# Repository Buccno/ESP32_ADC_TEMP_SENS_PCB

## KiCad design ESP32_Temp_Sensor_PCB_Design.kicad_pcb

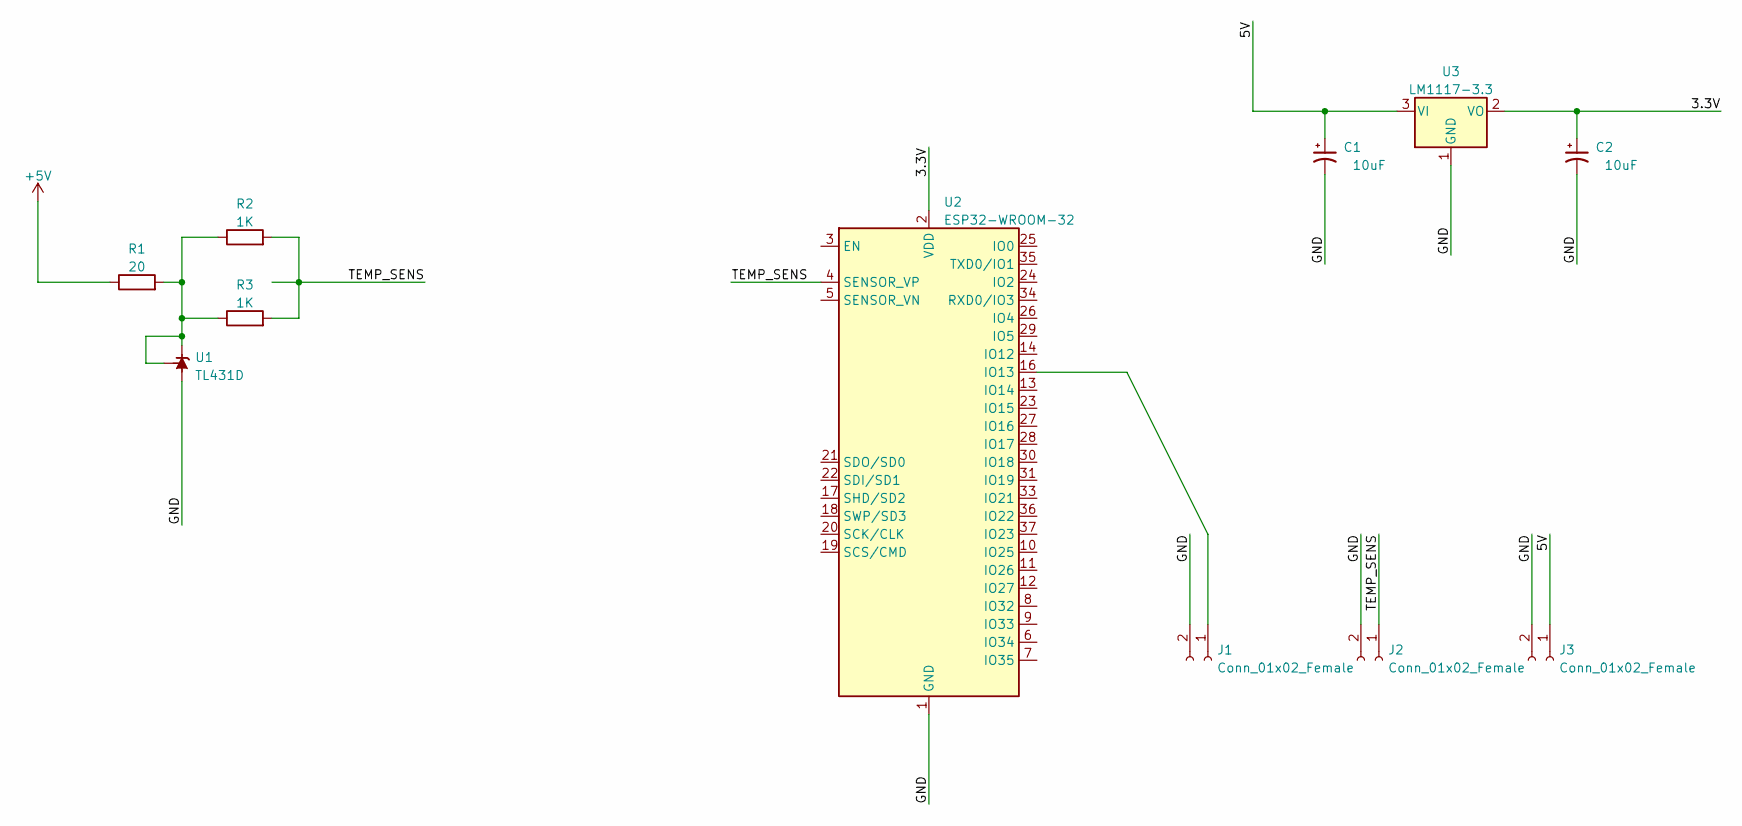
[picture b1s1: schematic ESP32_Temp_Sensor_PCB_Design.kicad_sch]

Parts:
C1, C2: 10uF; C_Elec_4x5.8; Manufacturer Part Number EEE-FK1C100R
J1, J2, J3: Conn_01x02_Female; PinHeader_1x02_P1.27mm_Vertical
R1: 20; R_0402_1005Metric
R2, R3: 1K; R_0402_1005Metric
U1: TL431D; SOIC-8_3.9x4.9mm_P1.27mm
U2: ESP32-WROOM-32
U3: LM1117-3.3; SOT230; Manufacturer Part Number LM1117DTX-3.3/NOPB

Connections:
+5V: R1.1
/3.3V: C2.1, U2.2 (VDD), U3.2 (VO)
/5V: C1.1, J3.1, U3.3 (VI)
/GND: C1.2, C2.2, J1.2, J2.2, J3.2, U1.2 (A), U1.3 (A), U1.6 (A), U1.7 (A), U2.1 (GND), U2.15 (GND), U2.38 (GND), U2.39 (GND), U3.1 (GND)
/TEMP_SENS: J2.1, R2.2, R3.2, U2.4 (SENSOR_VP)
unnamed: R1.2, R2.1, R3.1, U1.1 (K), U1.8 (REF)
unnamed: J1.1, U2.16 (IO13)

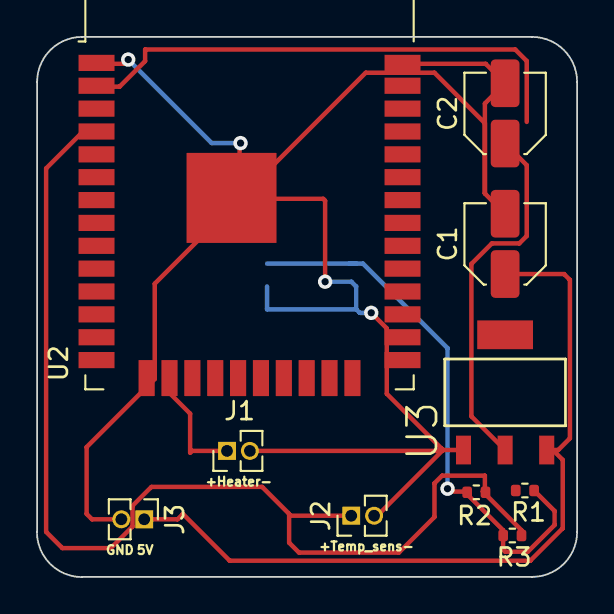
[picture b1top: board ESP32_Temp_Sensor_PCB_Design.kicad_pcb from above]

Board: 2 copper layers, 30.0 x 30.0 mm, 11 parts (1 on the bottom side), 6 nets.

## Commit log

2022-05-24 Added Kicad File
